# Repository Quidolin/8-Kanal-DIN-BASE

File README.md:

# 8-Kanal-DIN-BASE
Baseboard for HomeMatic HM-MOD-Re-8 and HM-MOD-EM-8 for DIN-Rail-Housing

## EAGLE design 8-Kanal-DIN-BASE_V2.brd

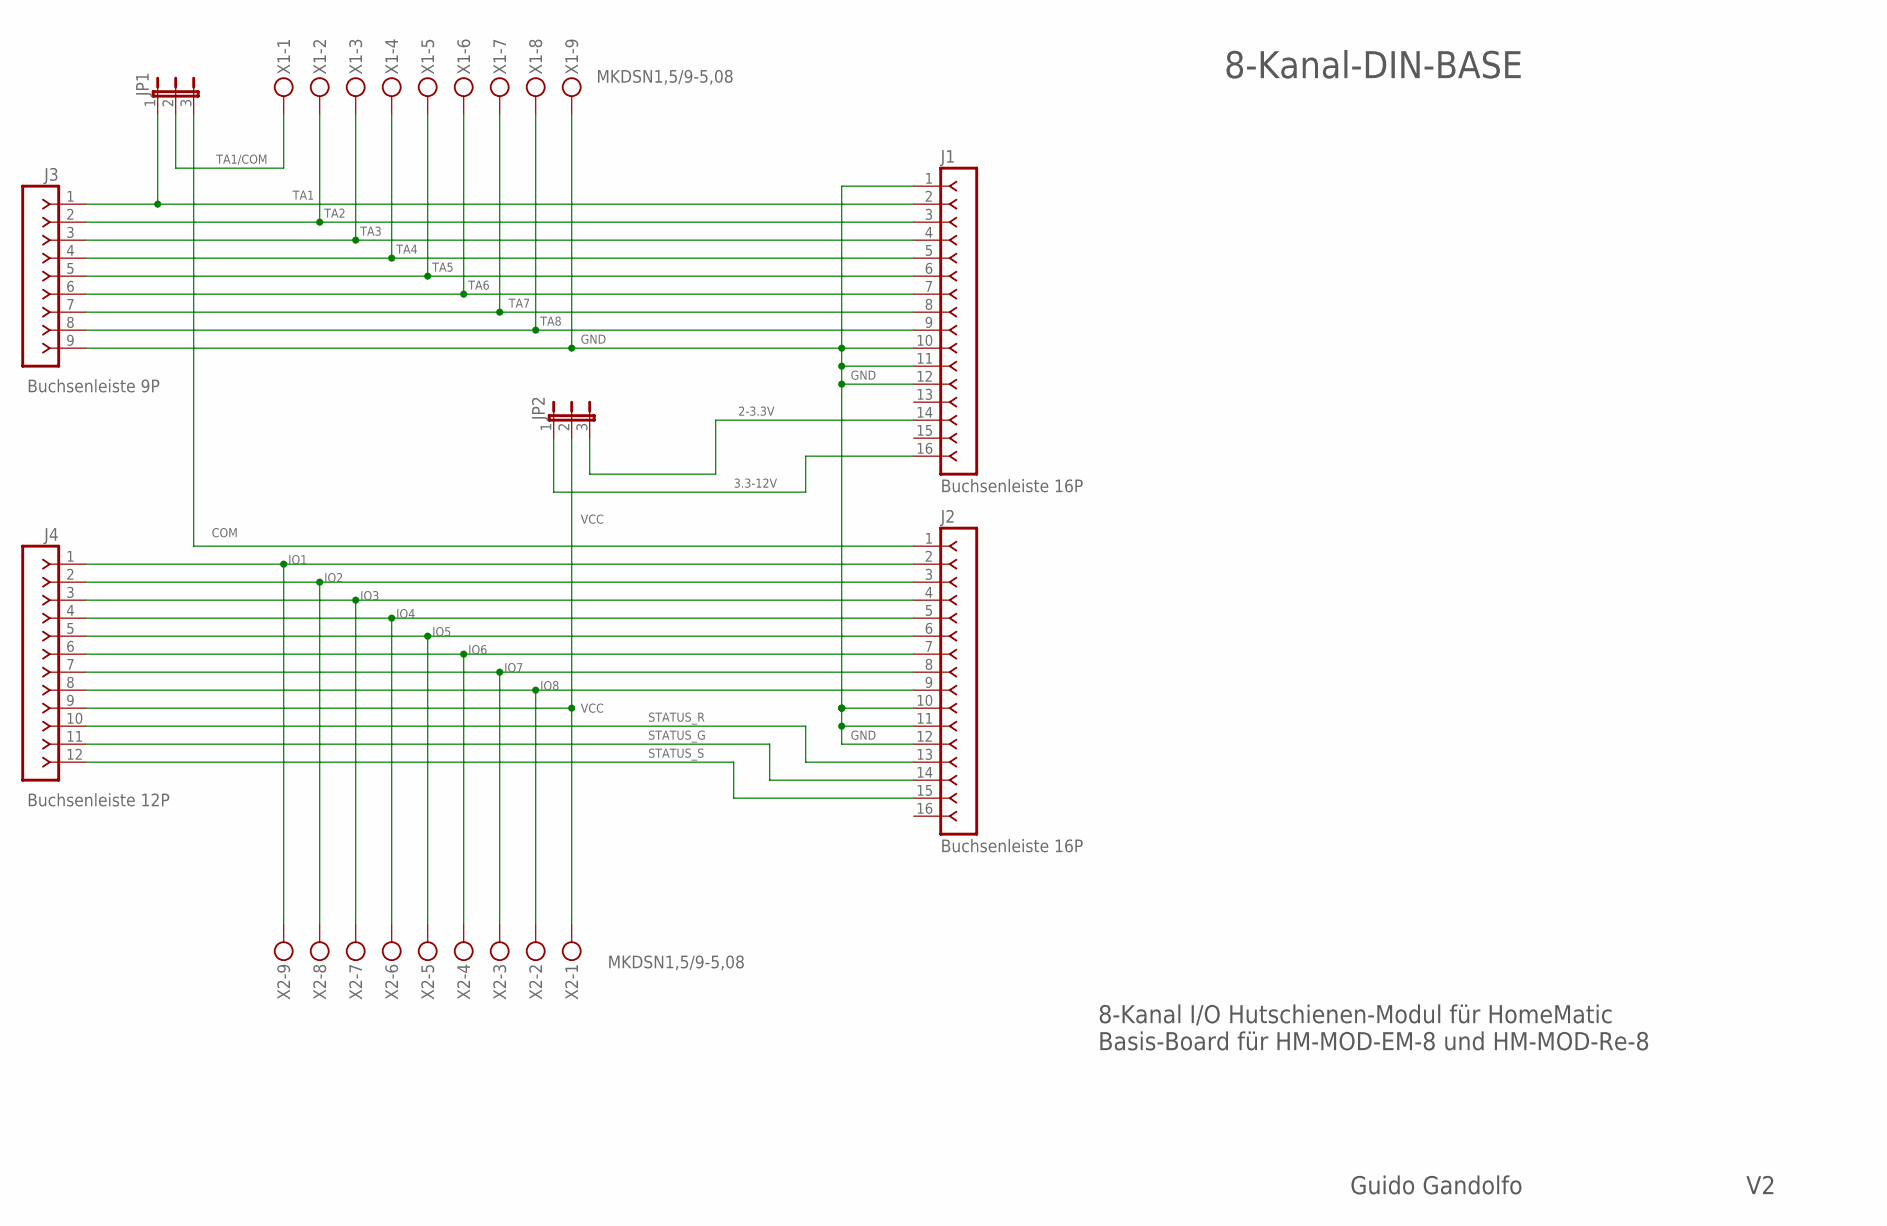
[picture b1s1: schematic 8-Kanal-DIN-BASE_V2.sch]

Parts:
J1, J2: Buchsenleiste 16P; SIP-100-16-40Y
J3: Buchsenleiste 9P; SIP-100-09-40Y
J4: Buchsenleiste 12P; SIP-100-12-40Y
JP1, JP2: JP2E; JP2
X1, X2: MKDSN1,5/9-5,08

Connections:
2-3.3V: J1.14, JP2.3
3.3-12V: J1.16, JP2.1
COM: J2.1, JP1.3
GND: J1.1, J1.10, J1.11, J1.12, J2.10, J2.11, J2.12, J3.9, X1.9
IO1: J2.2, J4.1, X2.9
IO2: J2.3, J4.2, X2.8
IO3: J2.4, J4.3, X2.7
IO4: J2.5, J4.4, X2.6
IO5: J2.6, J4.5, X2.5
IO6: J2.7, J4.6, X2.4
IO7: J2.8, J4.7, X2.3
IO8: J2.9, J4.8, X2.2
STATUS_G: J2.14, J4.11
STATUS_R: J2.13, J4.10
STATUS_S: J2.15, J4.12
TA1: J1.2, J3.1, JP1.1
TA1/COM: JP1.2, X1.1
TA2: J1.3, J3.2, X1.2
TA3: J1.4, J3.3, X1.3
TA4: J1.5, J3.4, X1.4
TA5: J1.6, J3.5, X1.5
TA6: J1.7, J3.6, X1.6
TA7: J1.8, J3.7, X1.7
TA8: J1.9, J3.8, X1.8
VCC: J4.9, JP2.2, X2.1

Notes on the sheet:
8-Kanal-DIN-BASE
8-Kanal I/O Hutschienen-Modul für HomeMatic Basis-Board für HM-MOD-EM-8 und HM-MOD-Re-8
Guido Gandolfo

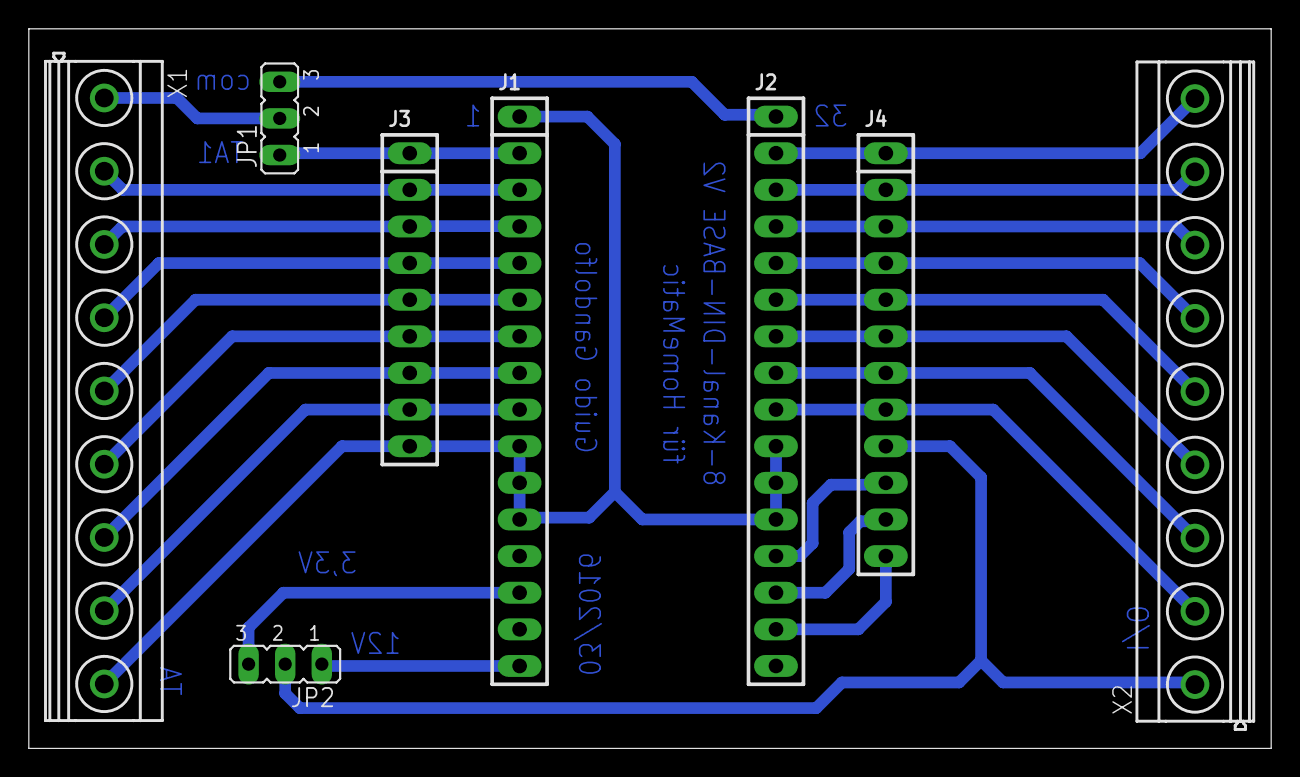
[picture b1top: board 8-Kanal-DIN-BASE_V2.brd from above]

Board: 2 copper layers, 86.2 x 49.9 mm, 8 parts (0 on the bottom side), 25 nets.

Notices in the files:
parts and their libraries:
con-headers-jp: Copyright (C) 2008, Bob Starr
